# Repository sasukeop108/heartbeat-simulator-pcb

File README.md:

# Heartbeat-simulator-pcb
This is a simple heartbeat simulator whikch i made using the ne555 ic,bc547 transistor and some other components. This was made for the hackclub stasis event. I made this totally using the kicad for schematic and pcb designing

# cart

# Schematic

# pcb

# 3d pcb

#bom

| Quantity | Component | Price | Link |
| :--- | :--- | :--- | :--- |
| 1 | ne555 ic | self sourced | NA |
| 2 | 1k resistors | self sourced | NA |
| 3 | potentiometer | self sourced | NA |
| 4 | capacitors | self sourced | NA |
| 5 | red leds | self sourced | NA |
| 6 | pcb | 11.77 usd | [://jlcpcb.com](https://://jlcpcb.com) |

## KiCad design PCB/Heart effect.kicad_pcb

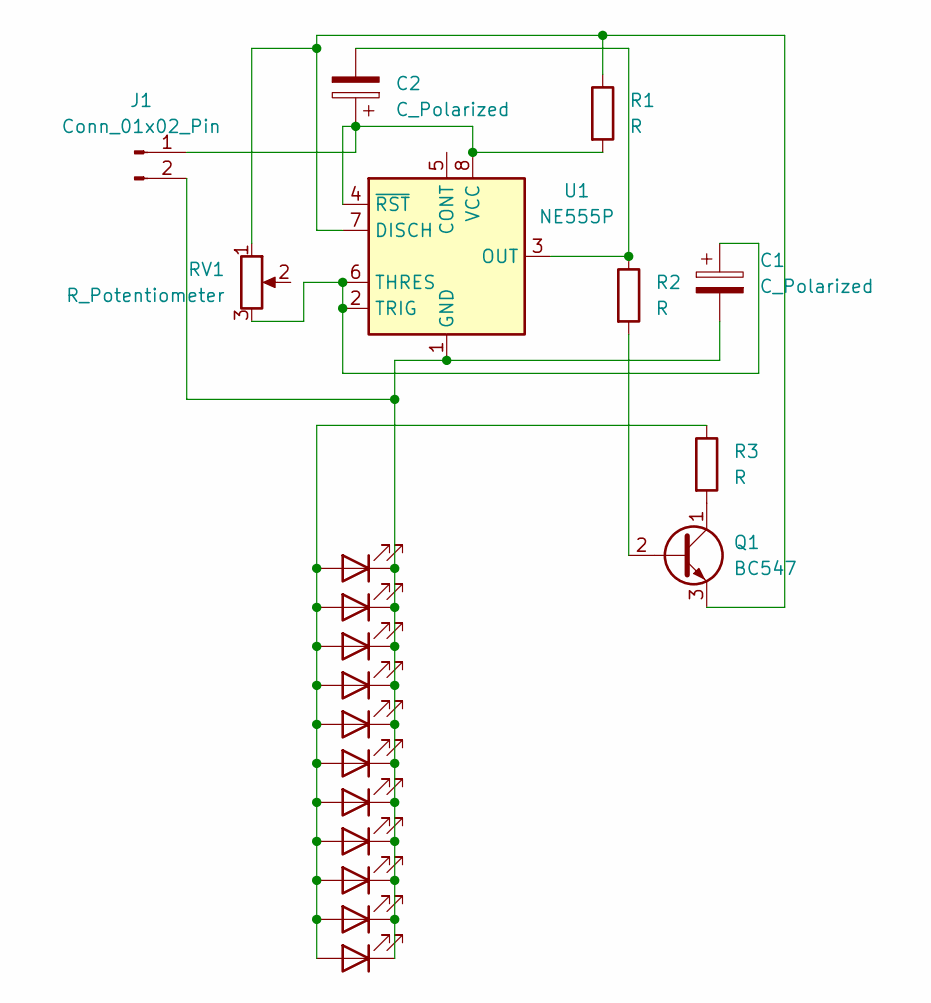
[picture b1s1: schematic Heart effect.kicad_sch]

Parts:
C1: C_Polarized; CP_Radial_D5.0mm_P2.00mm
C2: C_Polarized; CP_Radial_D6.3mm_P2.50mm
D1, D2, D3, D4, D5, D6, D7, D8, D9, D10, D11: LED; LED_D5.0mm
J1: Conn_01x02_Pin
Q1: BC547; TO-92_Inline
R1, R2, R3: R; R_Axial_DIN0207_L6.3mm_D2.5mm_P7.62mm_Horizontal
RV1: R_Potentiometer; Potentiometer_Runtron_RM-065_Vertical
U1: NE555P; DIP-8_W7.62mm

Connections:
unnamed: D1.2 (A), D2.2 (A), D3.2 (A), D4.2 (A), D5.2 (A), D6.2 (A), D7.2 (A), D8.2 (A), D9.2 (A), D10.2 (A), D11.2 (A), R3.1
unnamed: C1.2, D1.1 (K), D2.1 (K), D3.1 (K), D4.1 (K), D5.1 (K), D6.1 (K), D7.1 (K), D8.1 (K), D9.1 (K), D10.1 (K), D11.1 (K), J1.2, U1.1 (GND)
unnamed: Q1.2 (B), R2.2
unnamed: Q1.1 (C), R3.2
unnamed: Q1.3 (E), R1.1, RV1.1, U1.7 (DISCH)
unnamed: C2.2, R2.1, U1.3 (OUT)
unnamed: C1.1, RV1.3, U1.2 (TRIG), U1.6 (THRES)
unnamed: C2.1, J1.1, R1.2, U1.4 (~RST), U1.8 (VCC)

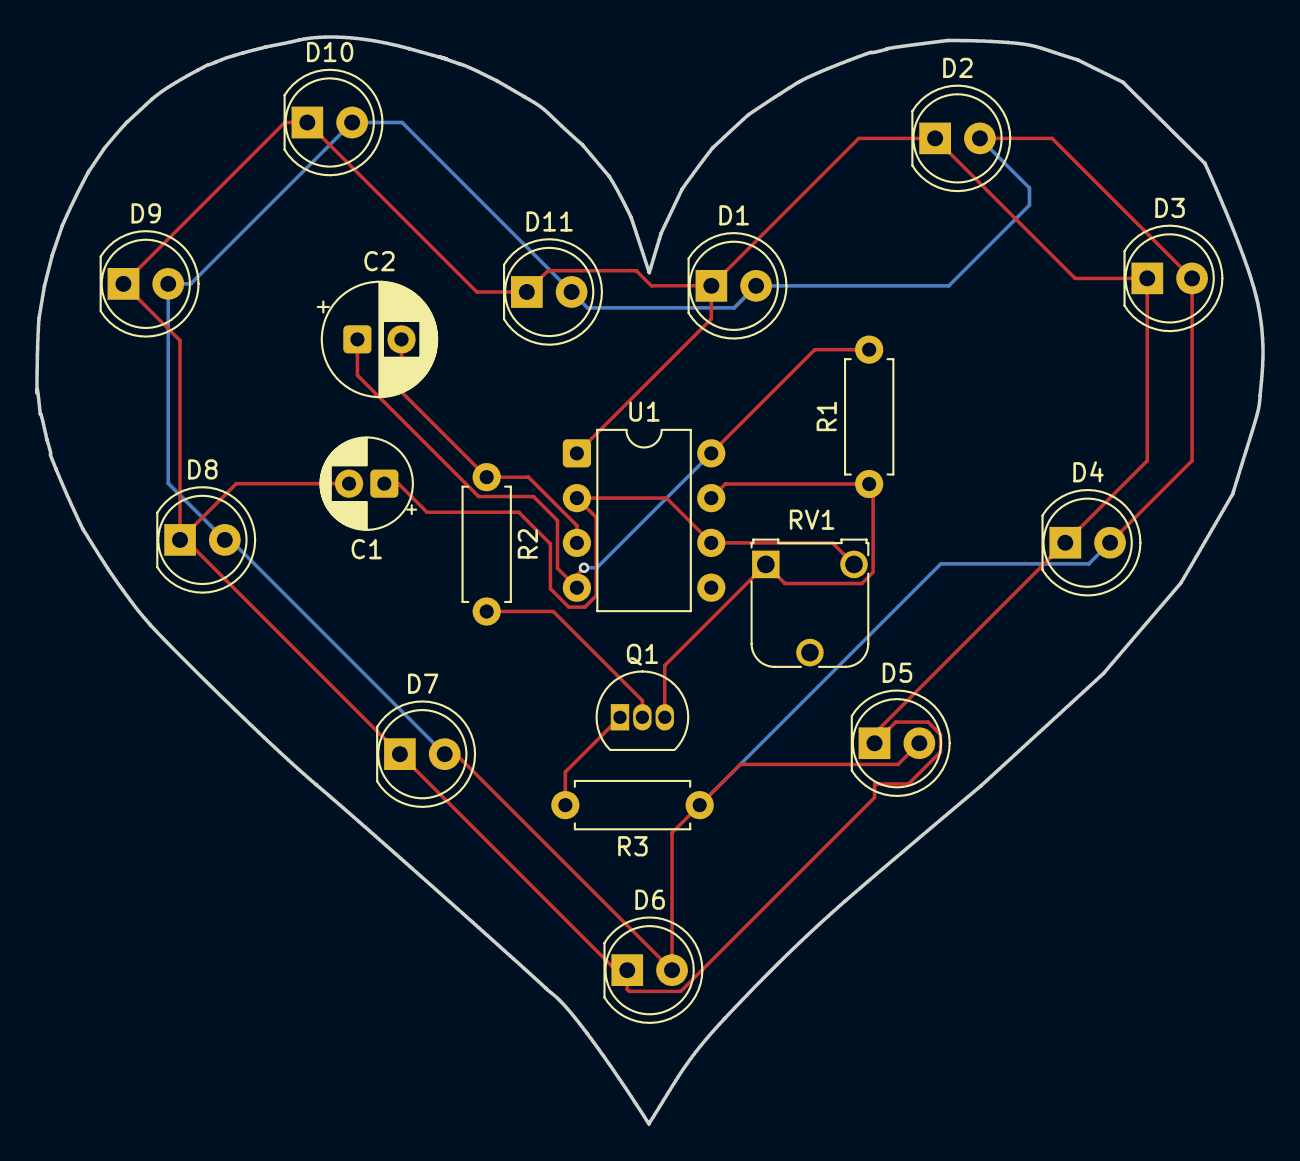
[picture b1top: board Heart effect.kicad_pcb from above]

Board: 2 copper layers, 69.5 x 61.6 mm, 19 parts (0 on the bottom side), 8 nets.

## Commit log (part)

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2026-04-26 Create s
2026-04-26 Create L
